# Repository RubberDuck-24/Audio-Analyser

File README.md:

# Audio-Analyser

PC-controlled audio analyzer with integrated dummy load for objective testing and calibration of audio amplifiers.

## Overview

This project provides a complete measurement chain for testing audio amplifiers — measuring key parameters like THD(+N), frequency response, and noise level. It replaces subjective "does it sound right?" evaluations with quantitative, reproducible, and logged results.

Developed as a bachelor project at Ingeniørhøjskolen, Aarhus University.

## Features

- **FFT-based spectrum analysis** with live updating display
- **THD+N measurement** at 1 kHz (and across frequency)
- **Internal loopback** via integrated DAC → ADC signal path
- **Dummy load** switchable between 4 Ω and 8 Ω, rated for ≥ 200 W
- **Over-temperature protection** with automatic relay cutoff (fail-safe)
- **Data logging** to CSV/JSON with date, DUT ID, load mode and sample rate
- **PDF report generation** with test info, results and FFT plots
- **24-bit / 192 kHz** dual-channel synchronous capture

## System Architecture

The signal chain is split into two branches:
- **Generator path**: PC → Teensy → DAC → Filter → DUT
- **Measurement path**: DUT → Attenuator → ADC → Teensy → PC

## Hardware

| Component | Description |
|-----------|-------------|
| Teensy 4.1 | MCU — USB High-Speed (480 Mbit/s), hardware I2S TX/RX |
| TI PCM4222EVM | 24-bit, 2-channel delta-sigma ADC |
| Adafruit PCM5102 | 32-bit I2S DAC, line-level output (~2.1 V RMS), no external control bus needed |
| Dummy Load | 16× 2 Ω/100 W resistors, 2-branch per channel configuration, relay-switched 4 Ω / 8 Ω |

## Repository Structure

Audio-Analyser/
- docs: Documentation, reports, measurements and pictures
- firmware: Teensy 4.1 firmware (PlatformIO / Arduino framework)
- software: PC-side Python application (FFT GUI, logging, reporting)

## Measurement Standards

Audio measurements are referenced against **DS/EN IEC 60268-3:2018** — *Sound system equipment, Part 3: Amplifiers* — used as a technical reference for parameters such as THD(+N), frequency response, and load conditions.

## Author

**Christian Rasmussen**

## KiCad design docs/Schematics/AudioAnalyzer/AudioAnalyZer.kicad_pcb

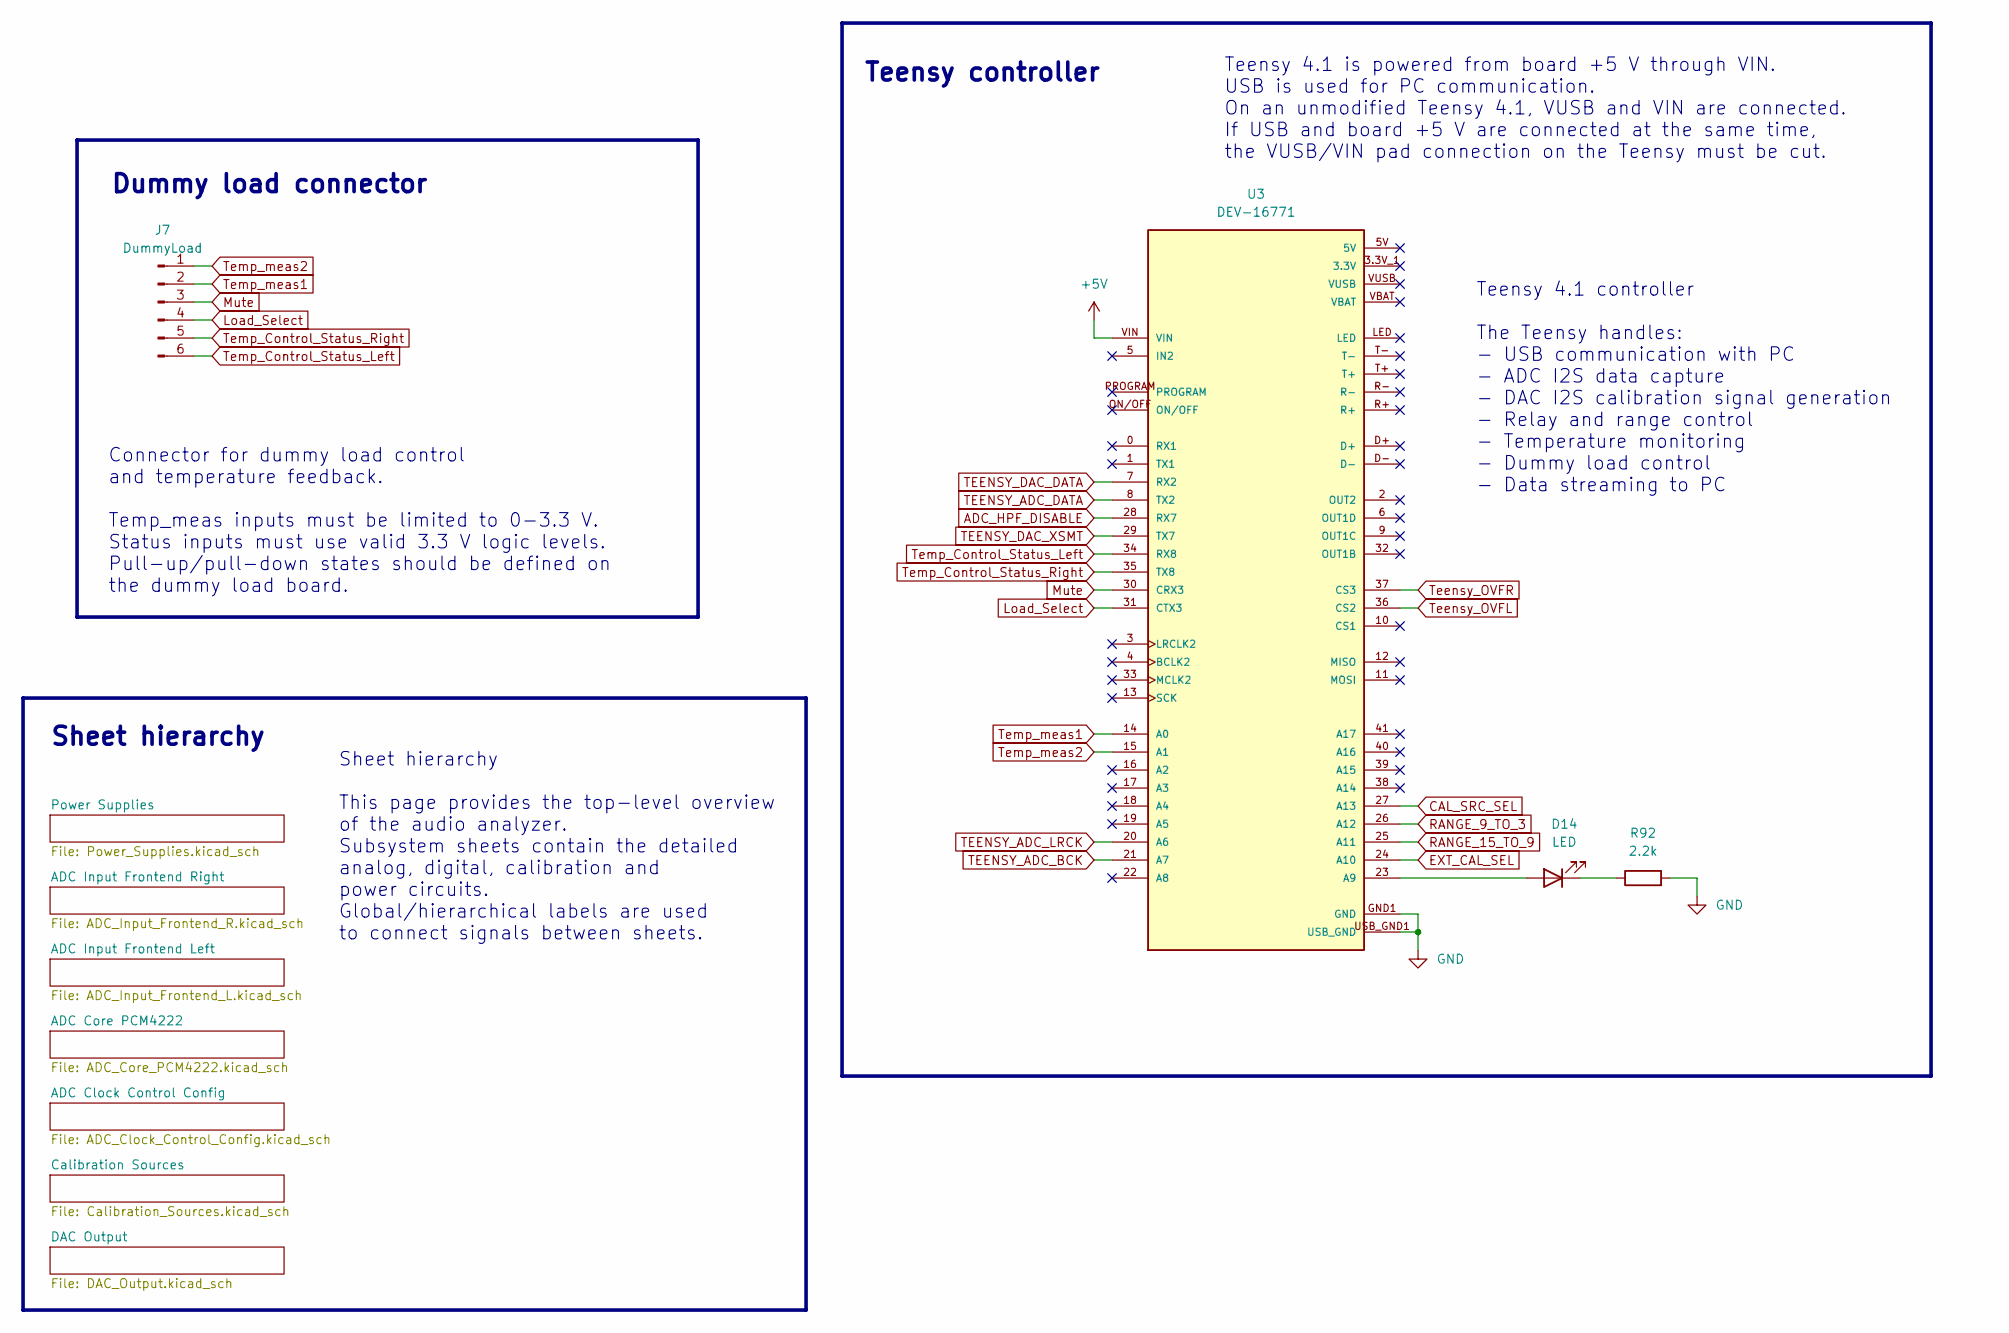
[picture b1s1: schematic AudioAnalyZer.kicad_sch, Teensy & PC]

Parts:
D14: LED; LED_0603_1608Metric_Pad1.05x0.95mm_HandSolder
J7: DummyLoad; PinHeader_1x06_P2.54mm_Horizontal
R92: 2.2k; R_0603_1608Metric_Pad0.98x0.95mm_HandSolder
U3: DEV-16771; MODULE_DEV-16771; PARTREV 4.1

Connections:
+5V: U3.VIN; also elsewhere on the board
ADC_HPF_DISABLE: U3.28 (RX7); also elsewhere on the board
CAL_SRC_SEL: U3.27 (A13); also elsewhere on the board
EXT_CAL_SEL: U3.24 (A10); also elsewhere on the board
GND: R92.2, U3.GND1 (GND), U3.GND2 (GND), U3.GND3 (GND), U3.GND4 (GND), U3.GND5 (GND), U3.USB_GND1 (USB_GND), U3.USB_GND2 (USB_GND); also elsewhere on the board
Load_Select: J7.4, U3.31 (CTX3)
Mute: J7.3, U3.30 (CRX3)
unnamed: D14.2 (A), U3.23 (A9)
unnamed: D14.1 (K), R92.1
RANGE_9_TO_3: U3.26 (A12); also elsewhere on the board
RANGE_15_TO_9: U3.25 (A11); also elsewhere on the board
TEENSY_ADC_BCK: U3.21 (A7); also elsewhere on the board
TEENSY_ADC_DATA: U3.8 (TX2); also elsewhere on the board
TEENSY_ADC_LRCK: U3.20 (A6); also elsewhere on the board
TEENSY_DAC_DATA: U3.7 (RX2); also elsewhere on the board
TEENSY_DAC_XSMT: U3.29 (TX7); also elsewhere on the board
Teensy_OVFL: U3.36 (CS2); also elsewhere on the board
Teensy_OVFR: U3.37 (CS3); also elsewhere on the board
Temp_Control_Status_Left: J7.6, U3.34 (RX8)
Temp_Control_Status_Right: J7.5, U3.35 (TX8)
Temp_meas1: J7.2, U3.14 (A0)
Temp_meas2: J7.1, U3.15 (A1)

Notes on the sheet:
Teensy controller
Teensy 4.1 controller The Teensy handles: - USB communication with PC - ADC I2S data capture - DAC I2S calibration signal generation - Relay and range control - Temperature monitoring - Dummy load control - Data streaming to PC
Teensy 4.1 is powered from board +5 V through VIN. USB is used for PC communication. On an unmodified Teensy 4.1, VUSB and VIN are connected. If USB and board +5 V are connected at the same time, the VUSB/VIN pad connection on the Teensy must be cut.
Sheet hierarchy This page provides the top-level overview of the audio analyzer. Subsystem sheets contain the detailed analog, digital, calibration and power circuits. Global/hierarchical labels are used to connect signals between sheets.
Connector for dummy load control and temperature feedback. Temp_meas inputs must be limited to 0-3.3 V. Status inputs must use valid 3.3 V logic levels. Pull-up/pull-down states should be defined on the dummy load board.
Dummy load connector
Sheet hierarchy

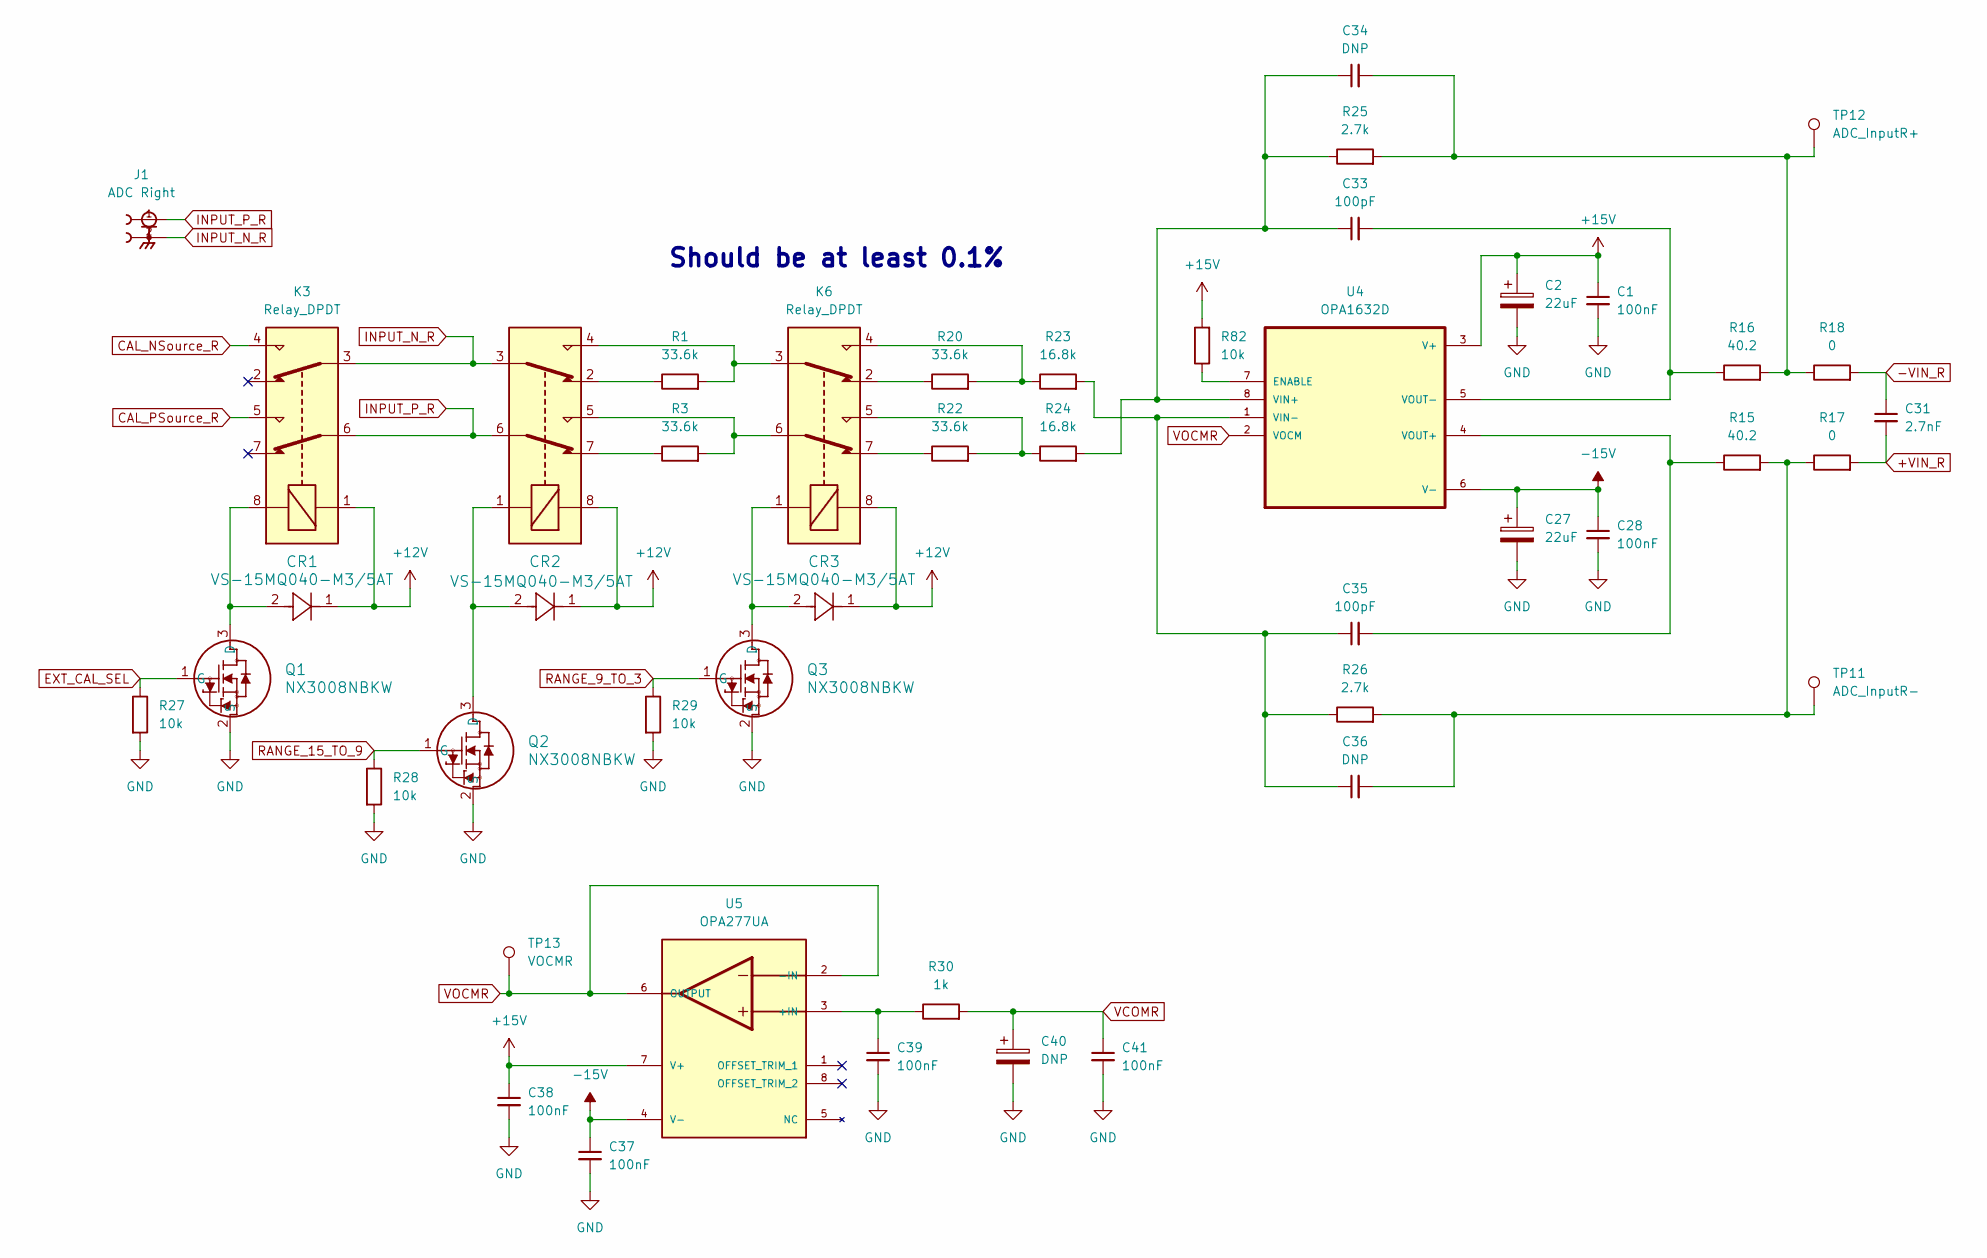
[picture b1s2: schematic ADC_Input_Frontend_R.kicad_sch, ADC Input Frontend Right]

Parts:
C1, C28, C37, C38, C39, C41: 100nF; C_0603_1608Metric_Pad1.08x0.95mm_HandSolder
C2, C27: 22uF; C_1206_3216Metric
C31: 2.7nF; C_0603_1608Metric
C33, C35: 100pF; C_0603_1608Metric_Pad1.08x0.95mm_HandSolder
C34, C36, C40: DNP; C_0603_1608Metric_Pad1.08x0.95mm_HandSolder
CR1, CR2, CR3: VS-15MQ040-M3/5AT; CR_Q040-M3&slash_5AT_VIS
J1: ADC Right; LINX_CONBNC002
K3, K5, K6: Relay_DPDT; RELAY_IM06DGR
Q1, Q2, Q3: NX3008NBKW; SC-70_SOT323_NEX
R1, R3, R20, R22: 33.6k; R_0603_1608Metric_Pad0.98x0.95mm_HandSolder
R15, R16: 40.2; R_0603_1608Metric_Pad0.98x0.95mm_HandSolder
R17, R18: 0; R_0603_1608Metric_Pad0.98x0.95mm_HandSolder
R23, R24: 16.8k; R_0603_1608Metric_Pad0.98x0.95mm_HandSolder
R25, R26: 2.7k; R_0603_1608Metric_Pad0.98x0.95mm_HandSolder
R27, R28, R29, R82: 10k; R_0603_1608Metric_Pad0.98x0.95mm_HandSolder
R30: 1k; R_0603_1608Metric_Pad0.98x0.95mm_HandSolder
TP11: ADC_InputR-; TestPoint_Pad_D1.5mm
TP12: ADC_InputR+; TestPoint_Pad_D1.5mm
TP13: VOCMR; TestPoint_Pad_D1.5mm
U4: OPA1632D; SOIC127P599X175-8N
U5: OPA277UA; SOIC127P599X175-8N; PARTREV 02/2019

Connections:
+12V: CR1.1, CR2.1, CR3.1, K3.1, K5.8, K6.8; also elsewhere on the board
+15V: C1.1, C2.1, C38.1, R82.2, U4.3 (V+), U5.7 (V+); also elsewhere on the board
+VIN_R: C31.2, R17.2; also elsewhere on the board
-15V: C27.1, C28.1, C37.1, U4.6 (V-), U5.4 (V-); also elsewhere on the board
-VIN_R: C31.1, R18.2; also elsewhere on the board
CAL_NSource_R: K3.4; also elsewhere on the board
CAL_PSource_R: K3.5; also elsewhere on the board
EXT_CAL_SEL: Q1.1 (G), R27.1; also elsewhere on the board
GND: C1.2, C2.2, C27.2, C28.2, C37.2, C38.2, C39.2, C40.2, C41.2, Q1.2 (S), Q2.2 (S), Q3.2 (S), R27.2, R28.2, R29.2; also elsewhere on the board
INPUT_N_R: J1.2, J1.S1, J1.S2, K3.3, K5.3
INPUT_P_R: J1.1, K3.6, K5.6
unnamed: C34.2, R16.2, R18.1, R25.2, TP12.1 (1_1)
unnamed: C36.2, R15.2, R17.1, R26.2, TP11.1 (1_1)
unnamed: K5.2, R1.1
unnamed: K5.4, K6.3, R1.2
unnamed: K5.5, K6.6, R3.2
unnamed: K5.7, R3.1
unnamed: K6.2, R20.1
unnamed: K6.4, R20.2, R23.1
unnamed: K6.5, R22.2, R24.1
unnamed: K6.7, R22.1
unnamed: CR1.2, K3.8, Q1.3 (D)
unnamed: CR2.2, K5.1, Q2.3 (D)
unnamed: CR3.2, K6.1, Q3.3 (D)
unnamed: R82.1, U4.7 (ENABLE)
unnamed: C33.1, C34.1, R24.2, R25.1, U4.8 (VIN+)
unnamed: C35.1, C36.1, R23.2, R26.1, U4.1 (VIN-)
unnamed: C35.2, R15.1, U4.4 (VOUT+)
unnamed: C33.2, R16.1, U4.5 (VOUT-)
unnamed: C39.1, R30.1, U5.3 (+IN)
RANGE_9_TO_3: Q3.1 (G), R29.1; also elsewhere on the board
RANGE_15_TO_9: Q2.1 (G), R28.1; also elsewhere on the board
VCOMR: C40.1, C41.1, R30.2; also elsewhere on the board
VOCMR: TP13.1 (1_1), U4.2 (VOCM), U5.2 (-IN), U5.6 (OUTPUT)

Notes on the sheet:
Should be at least 0.1%

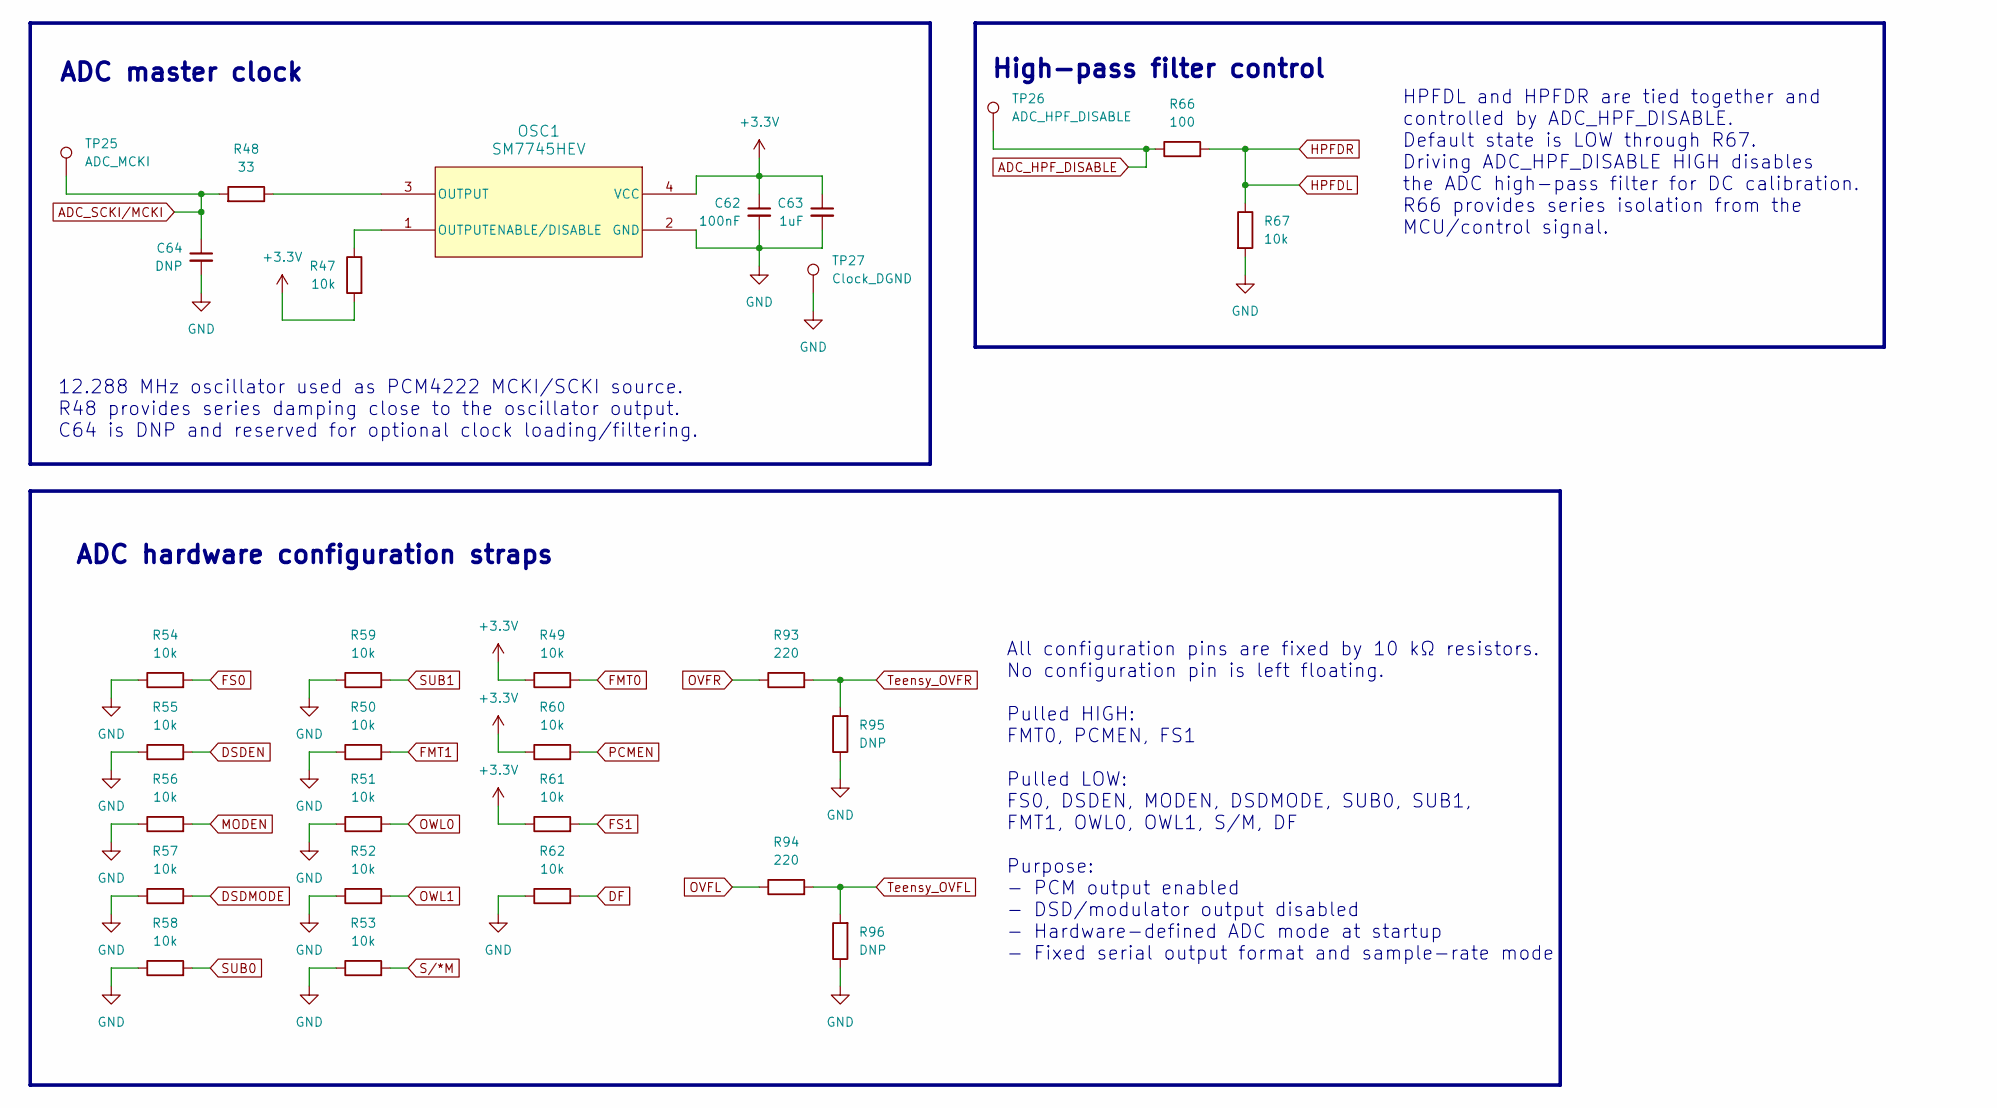
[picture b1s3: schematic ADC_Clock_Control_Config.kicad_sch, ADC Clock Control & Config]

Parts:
C62: 100nF; C_0603_1608Metric_Pad1.08x0.95mm_HandSolder
C63: 1uF; C_0603_1608Metric_Pad1.08x0.95mm_HandSolder
C64: DNP; C_0603_1608Metric_Pad1.08x0.95mm_HandSolder
OSC1: SM7745HEV; SM77H_PLT
R47, R49, R50, R51, R52, R53, R54, R55, R56, R57, R58, R59, R60, R61, R62, R67: 10k; R_0603_1608Metric_Pad0.98x0.95mm_HandSolder
R48: 33; R_0603_1608Metric_Pad0.98x0.95mm_HandSolder
R66: 100; R_0603_1608Metric_Pad0.98x0.95mm_HandSolder
R93, R94: 220; R_0603_1608Metric_Pad0.98x0.95mm_HandSolder
R95, R96: DNP; R_0603_1608Metric_Pad0.98x0.95mm_HandSolder
TP25: ADC_MCKI; TestPoint_Pad_D1.5mm
TP26: ADC_HPF_DISABLE; TestPoint_Pad_D1.5mm
TP27: Clock_DGND; TestPoint_Pad_D1.5mm

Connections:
+3.3V: C62.1, C63.1, OSC1.4 (VCC), R47.2, R49.1, R60.1, R61.1; also elsewhere on the board
ADC_HPF_DISABLE: R66.1, TP26.1 (1_1); also elsewhere on the board
ADC_SCKI/MCKI: C64.1, R48.2, TP25.1 (1_1); also elsewhere on the board
DF: R62.2; also elsewhere on the board
DSDEN: R55.2; also elsewhere on the board
DSDMODE: R57.2; also elsewhere on the board
FMT0: R49.2; also elsewhere on the board
FMT1: R50.2; also elsewhere on the board
FS0: R54.2; also elsewhere on the board
FS1: R61.2; also elsewhere on the board
GND: C62.2, C63.2, C64.2, OSC1.2 (GND), R50.1, R51.1, R52.1, R53.1, R54.1, R55.1, R56.1, R57.1, R58.1, R59.1, R62.1, R67.2, R95.1, R96.1, TP27.1 (1_1); also elsewhere on the board
HPFDL: R66.2, R67.1; also elsewhere on the board
MODEN: R56.2; also elsewhere on the board
unnamed: OSC1.3 (OUTPUT), R48.1
unnamed: OSC1.1 (OUTPUTENABLE/DISABLE), R47.1
OVFL: R94.1; also elsewhere on the board
OVFR: R93.1; also elsewhere on the board
OWL0: R51.2; also elsewhere on the board
OWL1: R52.2; also elsewhere on the board
PCMEN: R60.2; also elsewhere on the board
SUB0: R58.2; also elsewhere on the board
SUB1: R59.2; also elsewhere on the board
S/*M: R53.2; also elsewhere on the board
Teensy_OVFL: R94.2, R96.2; also elsewhere on the board
Teensy_OVFR: R93.2, R95.2; also elsewhere on the board

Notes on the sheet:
All configuration pins are fixed by 10 kΩ resistors. No configuration pin is left floating. Pulled HIGH: FMT0, PCMEN, FS1 Pulled LOW: FS0, DSDEN, MODEN, DSDMODE, SUB0, SUB1, FMT1, OWL0, OWL1, S/M, DF Purpose: - PCM output enabled - DSD/modulator output disabled - Hardware-defined ADC mode at startu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
ADC master clock
12.288 MHz oscillator used as PCM4222 MCKI/SCKI source. R48 provides series damping close to the oscillator output. C64 is DNP and reserved for optional clock loading/filtering.
ADC hardware configuration straps
High-pass filter control
HPFDL and HPFDR are tied together and controlled by ADC_HPF_DISABLE. Default state is LOW through R67. Driving ADC_HPF_DISABLE HIGH disables the ADC high-pass filter for DC calibration. R66 provides series isolation from the MCU/control signal.

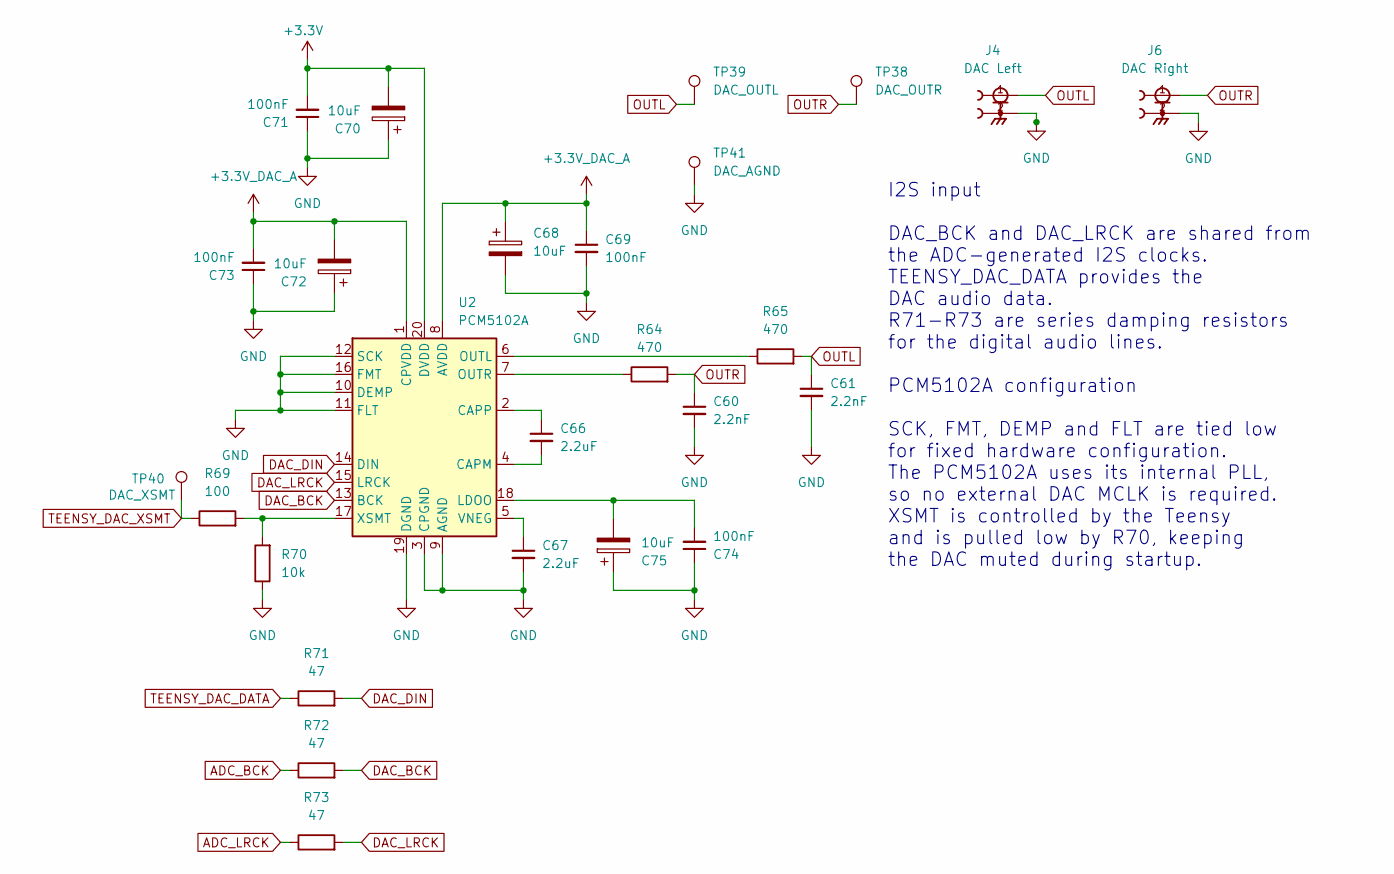
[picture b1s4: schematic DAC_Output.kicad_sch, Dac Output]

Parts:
C60, C61: 2.2nF; C_0603_1608Metric_Pad1.08x0.95mm_HandSolder
C66, C67: 2.2uF; C_1206_3216Metric
C68, C70, C72, C75: 10uF; C_0805_2012Metric
C69, C71, C73, C74: 100nF; C_0603_1608Metric_Pad1.08x0.95mm_HandSolder
J4: DAC Left; LINX_CONBNC002
J6: DAC Right; LINX_CONBNC002
R64, R65: 470; R_0603_1608Metric_Pad0.98x0.95mm_HandSolder
R69: 100; R_0603_1608Metric_Pad0.98x0.95mm_HandSolder
R70: 10k; R_0603_1608Metric_Pad0.98x0.95mm_HandSolder
R71, R72, R73: 47; R_0603_1608Metric_Pad0.98x0.95mm_HandSolder
TP38: DAC_OUTR; TestPoint_Pad_D1.5mm
TP39: DAC_OUTL; TestPoint_Pad_D1.5mm
TP40: DAC_XSMT; TestPoint_Pad_D1.5mm
TP41: DAC_AGND; TestPoint_Pad_D1.5mm
U2: PCM5102A; TSSOP-20_4.4x6.5mm_P0.65mm

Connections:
+3.3V: C70.2, C71.2, U2.20 (DVDD); also elsewhere on the board
+3.3V_DAC_A: C68.1, C69.1, C72.2, C73.2, U2.1 (CPVDD), U2.8 (AVDD); also elsewhere on the board
ADC_BCK: R72.1; also elsewhere on the board
ADC_LRCK: R73.1; also elsewhere on the board
DAC_BCK: R72.2, U2.13 (BCK)
DAC_DIN: R71.2, U2.14 (DIN)
DAC_LRCK: R73.2, U2.15 (LRCK)
GND: C60.2, C61.2, C67.2, C68.2, C69.2, C70.1, C71.1, C72.1, C73.1, C74.1, C75.1, J4.2, J4.S1, J4.S2, J6.2, J6.S1, J6.S2, R70.1, TP41.1 (1_1), U2.3 (CPGND), U2.9 (AGND), U2.10 (DEMP), U2.11 (FLT), U2.12 (SCK), U2.16 (FMT), U2.19 (DGND); also elsewhere on the board
unnamed: C66.2, U2.4 (CAPM)
unnamed: C66.1, U2.2 (CAPP)
unnamed: C74.2, C75.2, U2.18 (LDOO)
unnamed: R65.1, U2.6 (OUTL)
unnamed: R64.1, U2.7 (OUTR)
unnamed: C67.1, U2.5 (VNEG)
unnamed: R69.2, R70.2, U2.17 (XSMT)
OUTL: C61.1, J4.1, R65.2, TP39.1 (1_1); also elsewhere on the board
OUTR: C60.1, J6.1, R64.2, TP38.1 (1_1); also elsewhere on the board
TEENSY_DAC_DATA: R71.1; also elsewhere on the board
TEENSY_DAC_XSMT: R69.1, TP40.1 (1_1); also elsewhere on the board

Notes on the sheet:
I2S input DAC_BCK and DAC_LRCK are shared from the ADC-generated I2S clocks. TEENSY_DAC_DATA provides the DAC audio data. R71-R73 are series damping resistors for the digital audio lines. PCM5102A configuration SCK, FMT, DEMP and FLT are tied low for fixed hardware configuration. The PCM5102A uses 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

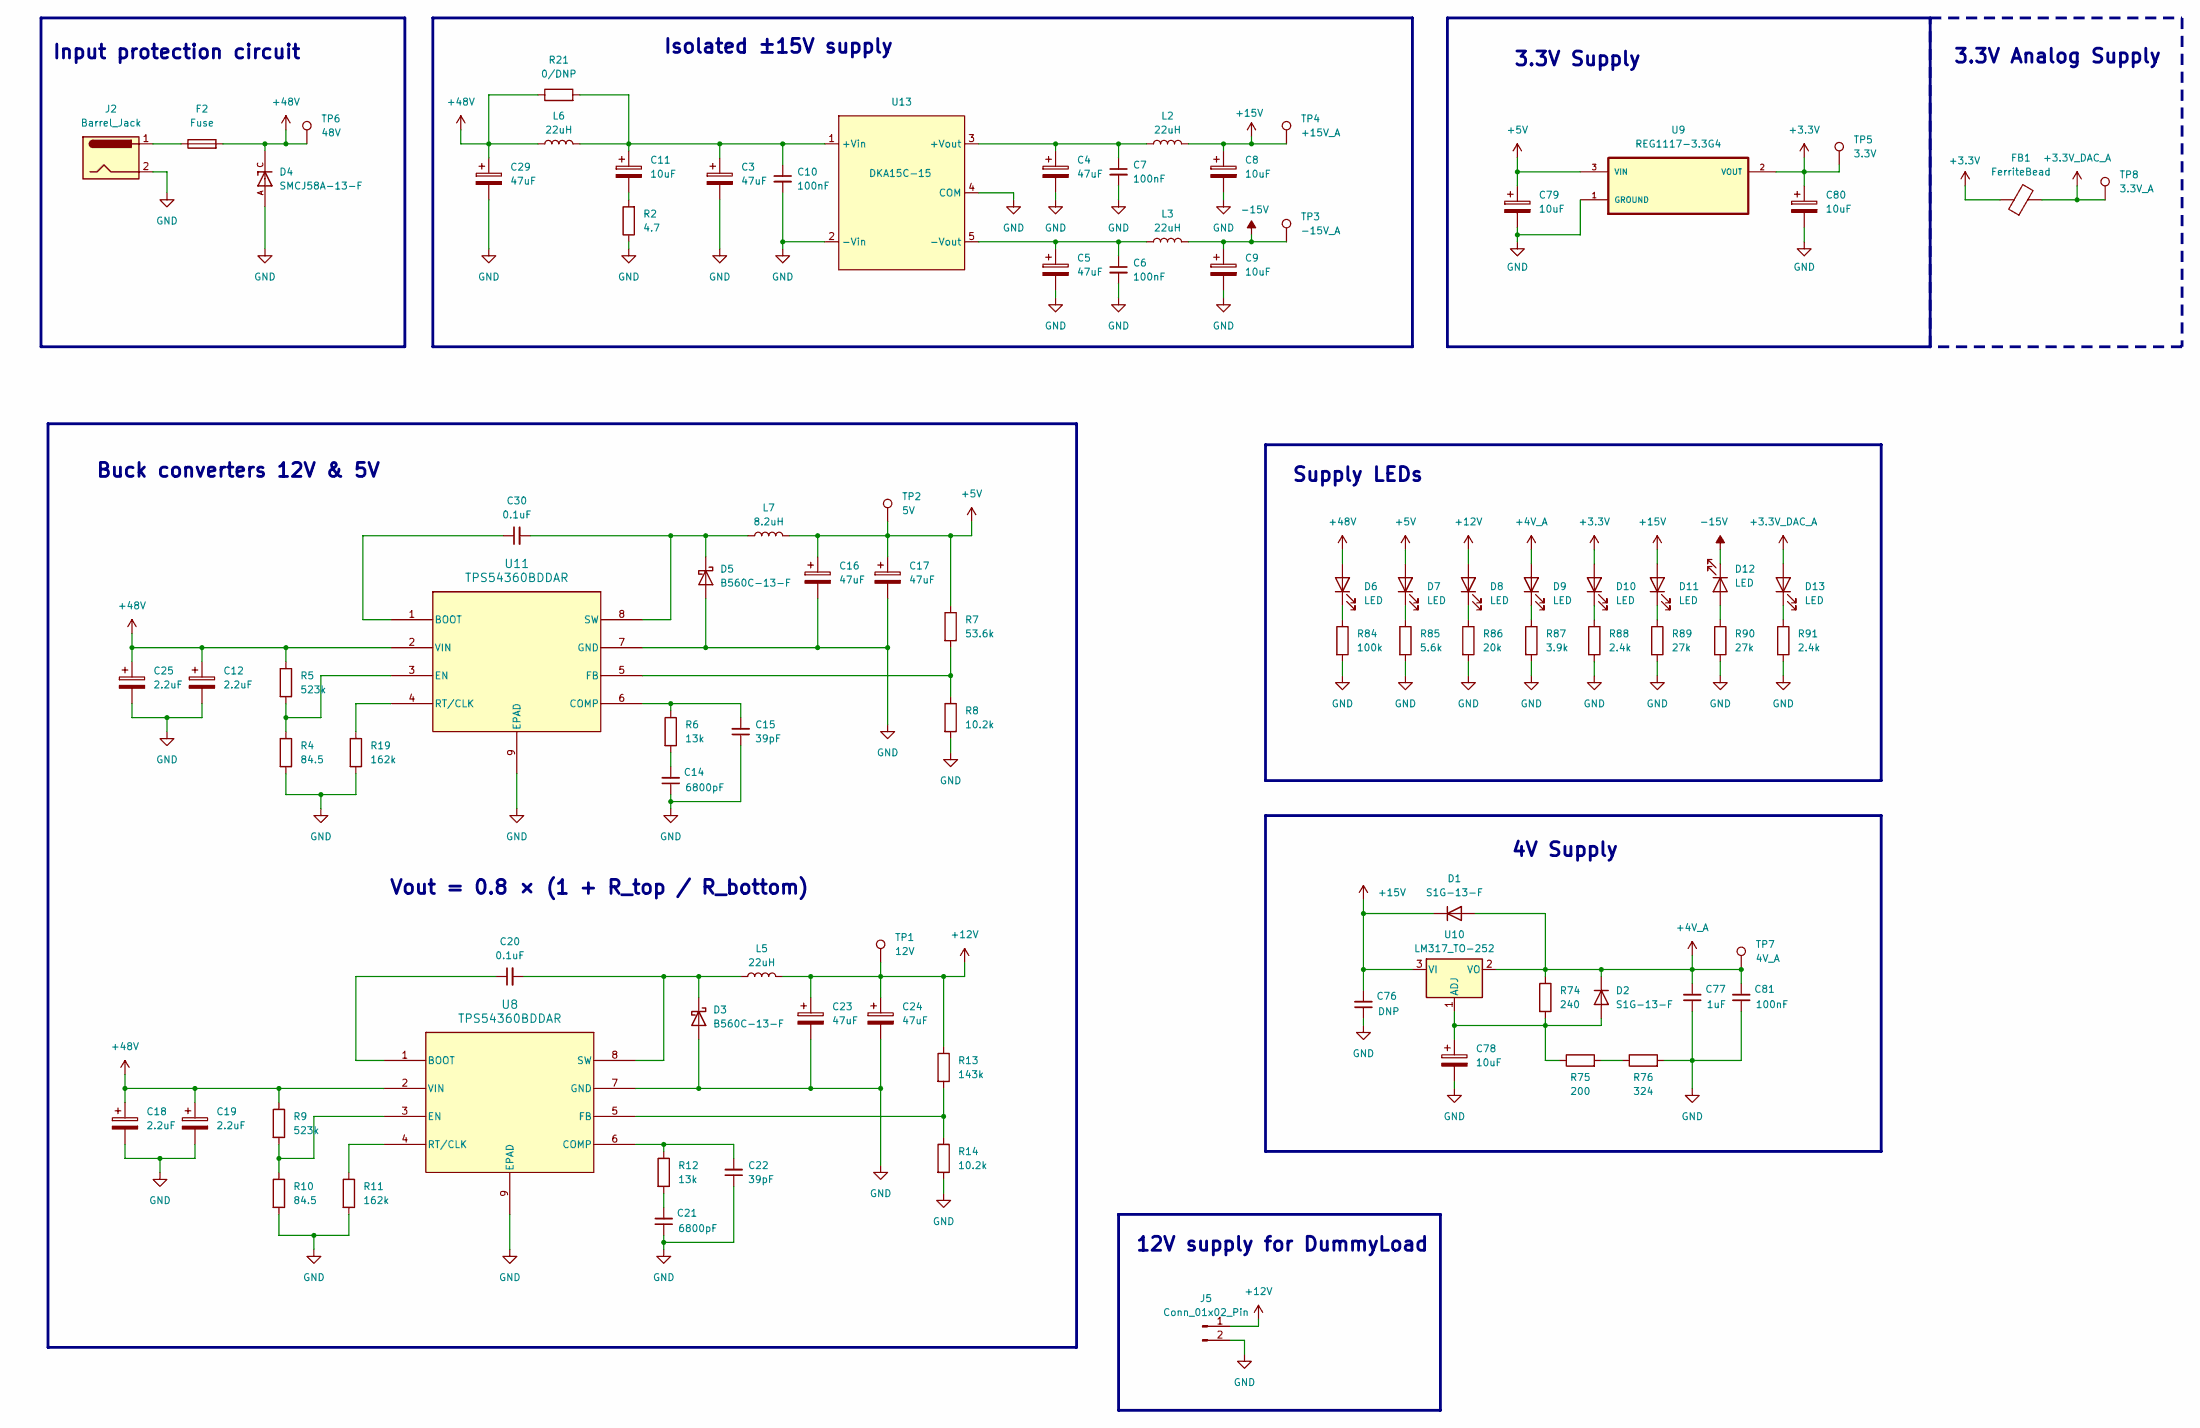
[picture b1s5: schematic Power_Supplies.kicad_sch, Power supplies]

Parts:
C3, C29: 47uF; CP_Elec_10x10.5
C4, C5, C23, C24: 47uF; CP_Elec_6.3x7.7
C6, C7, C81: 100nF; C_0603_1608Metric_Pad1.08x0.95mm_HandSolder
C8, C9: 10uF; C_1206_3216Metric
C10: 100nF; C_0805_2012Metric
C11: 10uF; CP_Elec_8x10.5
C12, C18, C19: 2.2uF; C_1210_3225Metric
C14, C21: 6800pF; C_0603_1608Metric_Pad1.08x0.95mm_HandSolder
C15, C22: 39pF; C_0603_1608Metric_Pad1.08x0.95mm_HandSolder
C16, C17: 47uF; C_1210_3225Metric
C20, C30: 0.1uF; C_0603_1608Metric_Pad1.08x0.95mm_HandSolder
C25: 2.2uF; C_1210_3225Metric_Pad1.33x2.70mm_HandSolder
C76: DNP; C_0603_1608Metric_Pad1.08x0.95mm_HandSolder
C77: 1uF; C_0603_1608Metric_Pad1.08x0.95mm_HandSolder
C78: 10uF; C_0805_2012Metric
C79, C80: 10uF; CP_EIA-3216-18_Kemet-A
D1, D2: S1G-13-F; D_SMA
D3, D5: B560C-13-F; D_SMC_Handsoldering
D4: SMCJ58A-13-F; DIOM7959X250N; PARTREV 5-2
D6, D7, D8, D9, D10, D11, D12, D13: LED; LED_0603_1608Metric_Pad1.05x0.95mm_HandSolder
F2: Fuse; 0451Series_LTF-M
FB1: FerriteBead; BEADC2012X105N
J2: Barrel_Jack; BarrelJack_CUI_PJ-063AH_Horizontal
J5: Conn_01x02_Pin; PhoenixContact_MSTBA_2,5_2-G-5,08_1x02_P5.08mm_Horizontal
L2, L3, L5, L6: 22uH; IND_HCM1A0805V2_EAT-L
L7: 8.2uH; WE-PD_1030P
R2: 4.7; R_1206_3216Metric_Pad1.30x1.75mm_HandSolder
R4, R10: 84.5; R_0603_1608Metric_Pad0.98x0.95mm_HandSolder
R5, R9: 523k; R_0805_2012Metric_Pad1.20x1.40mm_HandSolder
R6, R12: 13k; R_0603_1608Metric_Pad0.98x0.95mm_HandSolder
R7: 53.6k; R_0603_1608Metric_Pad0.98x0.95mm_HandSolder
R8, R14: 10.2k; R_0603_1608Metric_Pad0.98x0.95mm_HandSolder
R11, R19: 162k; R_0603_1608Metric_Pad0.98x0.95mm_HandSolder
R13: 143k; R_0603_1608Metric_Pad0.98x0.95mm_HandSolder
R21: 0/DNP; R_0603_1608Metric_Pad0.98x0.95mm_HandSolder
R74: 240; R_0603_1608Metric_Pad0.98x0.95mm_HandSolder
R75: 200; R_0603_1608Metric_Pad0.98x0.95mm_HandSolder
R76: 324; R_0603_1608Metric_Pad0.98x0.95mm_HandSolder
R84: 100k; R_1206_3216Metric_Pad1.30x1.75mm_HandSolder
R85: 5.6k; R_0603_1608Metric_Pad0.98x0.95mm_HandSolder
R86: 20k; R_0603_1608Metric_Pad0.98x0.95mm_HandSolder
R87: 3.9k; R_0603_1608Metric_Pad0.98x0.95mm_HandSolder
R88, R91: 2.4k; R_0603_1608Metric_Pad0.98x0.95mm_HandSolder
R89, R90: 27k; R_0603_1608Metric_Pad0.98x0.95mm_HandSolder
TP1: 12V; TestPoint_Pad_D1.5mm
TP2: 5V; TestPoint_Pad_D1.5mm
TP3: -15V_A; TestPoint_Pad_D1.5mm
TP4: +15V_A; TestPoint_Pad_D1.5mm
TP5: 3.3V; TestPoint_Pad_D1.5mm
TP6: 48V; TestPoint_Pad_D1.5mm
TP7: 4V_A; TestPoint_Pad_D1.5mm
TP8: 3.3V_A; TestPoint_Pad_D1.5mm
U8, U11: TPS54360BDDAR; U_DDA_TEX-M
U9: REG1117-3.3G4; SOT230P700X180-4N
U10: LM317_TO-252; TO-252-2
U13: DKA15C-15; DKA15C

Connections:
+3.3V: C80.1, D10.2 (A), FB1.1, TP5.1 (1_1), U9.2 (VOUT), U9.4 (VOUT); also elsewhere on the board
+3.3V_DAC_A: D13.2 (A), FB1.2, TP8.1 (1_1); also elsewhere on the board
+4V_A: C77.2, C81.2, D1.2 (A), D2.1 (K), D9.2 (A), R74.1, TP7.1 (1_1), U10.2 (VO); also elsewhere on the board
+5V: C16.1, C17.1, C79.1, D7.2 (A), L7.2, R7.1, TP2.1 (1_1), U9.3 (VIN); also elsewhere on the board
+12V: C23.1, C24.1, D8.2 (A), J5.1, L5.2, R13.1, TP1.1 (1_1); also elsewhere on the board
+15V: C8.1, C76.2, D1.1 (K), D11.2 (A), L2.2, TP4.1 (1_1), U10.3 (VI); also elsewhere on the board
+48V: C12.1, C18.1, C19.1, C25.1, C29.1, D4.C, D6.2 (A), F2.2, L6.1, R5.1, R9.1, R21.1, TP6.1 (1_1), U8.2 (VIN), U11.2 (VIN)
-15V: C9.1, D12.1 (K), L3.2, TP3.1 (1_1); also elsewhere on the board
GND: C3.2, C4.2, C5.2, C6.2, C7.2, C8.2, C9.2, C10.2, C12.2, C14.1, C15.1, C16.2, C17.2, C18.2, C19.2, C21.1, C22.1, C23.2, C24.2, C25.2, C29.2, C76.1, C77.1, C78.2, C79.2, C80.2, C81.1, D3.2 (A), D4.A, D5.2 (A), J2.2, J2.MP, J5.2, R2.1, R4.2, R8.2, R10.2, R11.2, R14.2, R19.2, R76.2, R84.2, R85.2, R86.2, R87.2, R88.2, R89.2, R90.2, R91.2, U8.7 (GND), U8.9 (EPAD), U8.EPAD, U9.1 (GROUND), U11.7 (GND), U11.9 (EPAD), U11.EPAD, U13.2 (-Vin), U13.4 (COM); also elsewhere on the board
unnamed: C11.2, R2.2
unnamed: C14.2, R6.2
unnamed: C21.2, R12.2
unnamed: C78.1, D2.2 (A), R74.2, R75.1, U10.1 (ADJ)
unnamed: C20.2, D3.1 (K), L5.1, U8.8 (SW)
unnamed: C30.2, D5.1 (K), L7.1, U11.8 (SW)
unnamed: D6.1 (K), R84.1
unnamed: D7.1 (K), R85.1
unnamed: D8.1 (K), R86.1
unnamed: D9.1 (K), R87.1
unnamed: D10.1 (K), R88.1
unnamed: D11.1 (K), R89.1
unnamed: D12.2 (A), R90.1
unnamed: D13.1 (K), R91.1
unnamed: F2.1, J2.1
unnamed: R75.2, R76.1
unnamed: C20.1, U8.1 (BOOT)
unnamed: C22.2, R12.1, U8.6 (COMP)
unnamed: R9.2, R10.1, U8.3 (EN)
unnamed: R13.2, R14.1, U8.5 (FB)
unnamed: R11.1, U8.4 (RT/CLK)
unnamed: C30.1, U11.1 (BOOT)
unnamed: C15.2, R6.1, U11.6 (COMP)
unnamed: R4.1, R5.2, U11.3 (EN)
unnamed: R7.2, R8.1, U11.5 (FB)
unnamed: R19.1, U11.4 (RT/CLK)
unnamed: C3.1, C10.1, C11.1, L6.2, R21.2, U13.1 (+Vin)
unnamed: C4.1, C7.1, L2.1, U13.3 (+Vout)
unnamed: C5.1, C6.1, L3.1, U13.5 (-Vout)

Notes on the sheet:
3.3V Analog Supply
Input protection circuit
Vout = 0.8 × (1 + R_top / R_bottom)
Buck converters 12V & 5V
Supply LEDs
4V Supply
3.3V Supply
Isolated ±15V supply
12V supply for DummyLoad
